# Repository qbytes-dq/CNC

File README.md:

# CNC
CNC projects

This project is for users to build a CNC projects. 

Components included are:
- PCB Etching
- etc...

TAGs will be created upon projects being available, not every commit.

SCH files are Eagle schematics.

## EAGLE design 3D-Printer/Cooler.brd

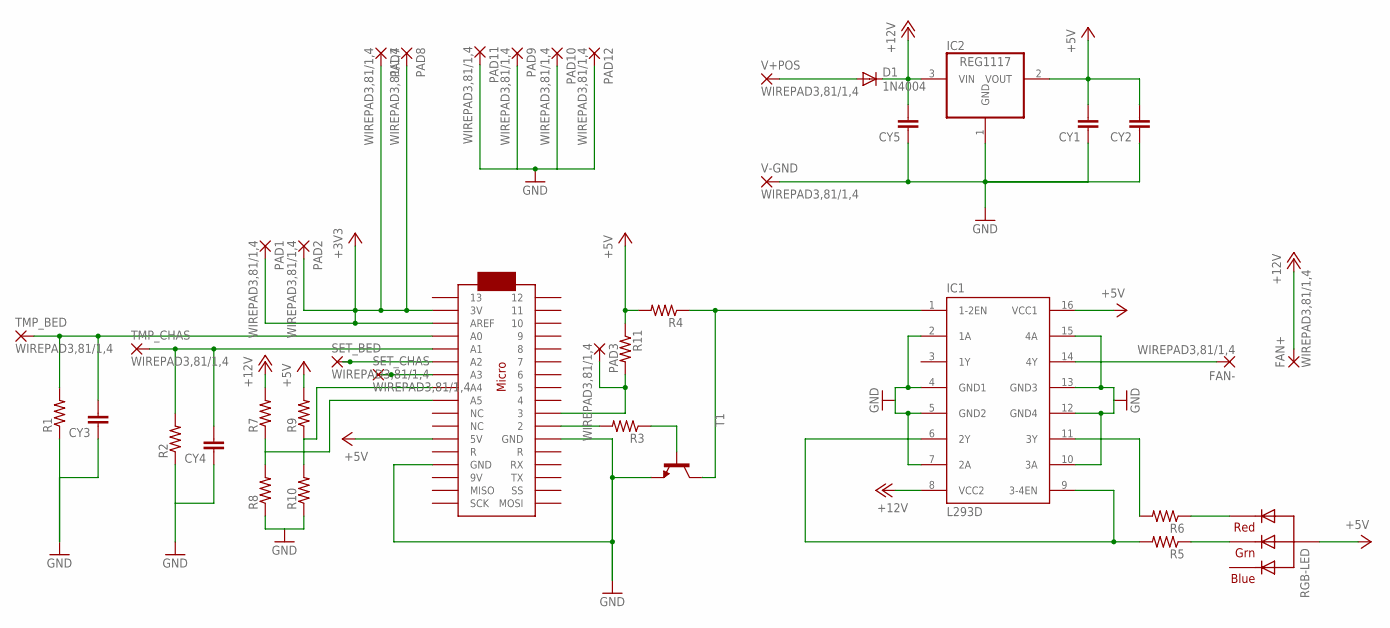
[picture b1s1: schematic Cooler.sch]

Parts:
CY1, CY2, CY3, CY4, CY5: CYYC7B5; YC7B5
D1: 1N4004; DO41-10
FAN+: WIREPAD3,81/1,4; 3,81/1,4
FAN-: WIREPAD3,81/1,4; 3,81/1,4
IC1: L293D; DIL16
IC2: REG1117; SOT223
PAD1, PAD2, PAD3, PAD7, PAD8, PAD9, PAD10, PAD11, PAD12: WIREPAD3,81/1,4; 3,81/1,4
R1, R2, R3, R4, R8, R10, R11: R-US_0309/10; 0309/10
R5, R6, R7, R9: R-US_0309/12; 0309/12
RGB-LED: RGBLED_CA-5MM; LED5MMRGB
SET_BED: WIREPAD3,81/1,4; 3,81/1,4
SET_CHAS: WIREPAD3,81/1,4; 3,81/1,4
T1: 2N2222-NPN-TO92-EBC; TO92-EBC
TMP_BED: WIREPAD3,81/1,4; 3,81/1,4
TMP_CHAS: WIREPAD3,81/1,4; 3,81/1,4
U$1: ARDUINOMICRO
V+POS: WIREPAD3,81/1,4; 3,81/1,4
V-GND: WIREPAD3,81/1,4; 3,81/1,4

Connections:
+3V3: PAD1.1, PAD2.1, PAD7.1, PAD8.1, U$1.P$32 (AREF), U$1.P$33 (3V)
+5V: CY1.2, CY2.2, IC1.16 (VCC1), IC2.2 (VOUT), R4.2, R9.2, R11.1, RGB-LED.2 (VCC), U$1.P$23 (5V)
+12V: CY5.2, D1.C, FAN+.1, IC1.8 (VCC2), IC2.3 (VIN), R7.2
GND: CY1.1, CY2.1, CY3.1, CY4.1, CY5.1, IC1.2 (1A), IC1.4 (GND1), IC1.5 (GND2), IC1.7 (2A), IC1.10 (3A), IC1.12 (GND4), IC1.13 (GND3), IC1.15 (4A), IC2.1 (GND), PAD9.1, PAD10.1, PAD11.1, PAD12.1, R1.1, R2.1, R8.1, R10.1, T1.E, U$1.P$12 (GND), U$1.P$21 (GND), V-GND.1
unnamed: R3.1, T1.B
unnamed: CY3.2, R1.2, TMP_BED.1, U$1.P$31 (A0)
unnamed: IC1.1 (1-2EN), R4.1, T1.C
unnamed: CY4.2, R2.2, TMP_CHAS.1, U$1.P$30 (A1)
unnamed: IC1.6 (2Y), IC1.9 (3-4EN), R5.2
unnamed: IC1.11 (3Y), R6.2
unnamed: R6.1, RGB-LED.1 (RED)
unnamed: R5.1, RGB-LED.3 (GREEN)
unnamed: FAN-.1, IC1.14 (4Y)
unnamed: D1.A, V+POS.1
unnamed: R3.2, U$1.P$11 (2)
unnamed: PAD3.1, R11.2, U$1.P$10 (3)
unnamed: SET_BED.1, U$1.P$29 (A2)
unnamed: SET_CHAS.1, U$1.P$28 (A3)
unnamed: R7.1, R8.2, U$1.P$26 (A5)
unnamed: R9.1, R10.2, U$1.P$27 (A4)

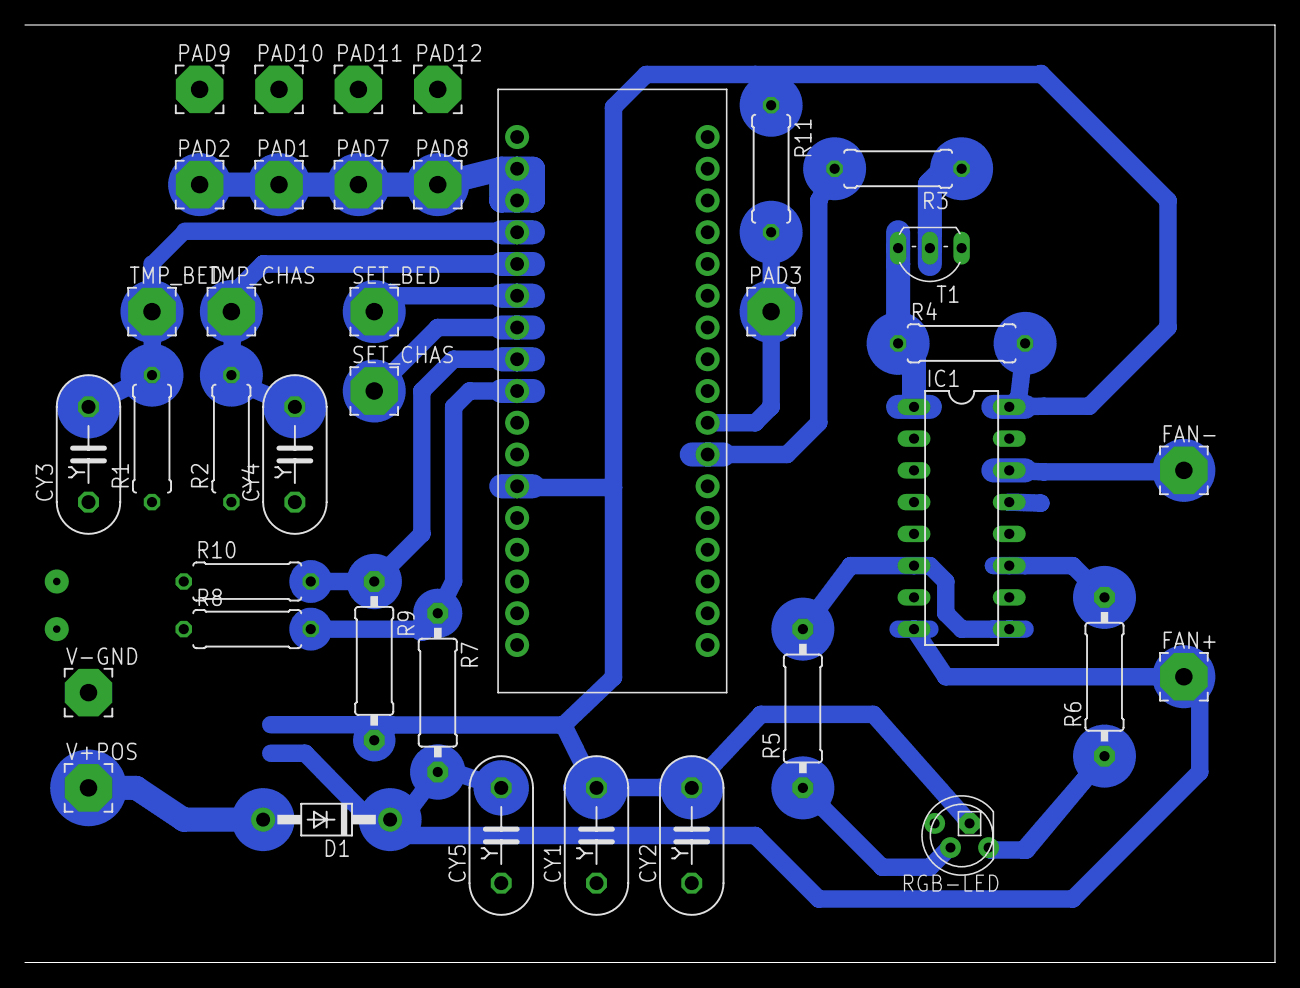
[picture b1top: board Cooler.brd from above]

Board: 2 copper layers, 100.0 x 75.0 mm, 39 parts (1 on the bottom side), 20 nets.

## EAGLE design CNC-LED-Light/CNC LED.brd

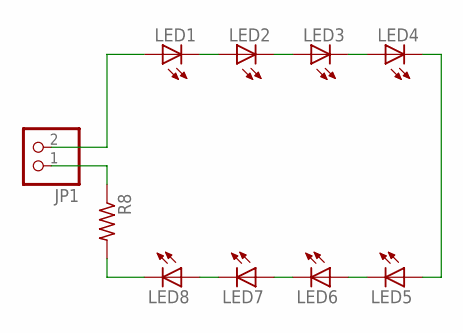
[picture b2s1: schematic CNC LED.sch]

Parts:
JP1: PINHD-1X2; 1X02
LED1, LED2, LED3, LED4, LED5, LED6, LED7, LED8: LEDCHIPLED_1206; CHIPLED_1206
R8: R-US_R1206; R1206

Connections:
unnamed: LED1.C, LED2.A
unnamed: JP1.1, R8.1
unnamed: LED2.C, LED3.A
unnamed: LED3.C, LED4.A
unnamed: LED8.C, R8.2
unnamed: LED4.C, LED5.A
unnamed: LED5.C, LED6.A
unnamed: LED6.C, LED7.A
unnamed: LED7.C, LED8.A
unnamed: JP1.2, LED1.A

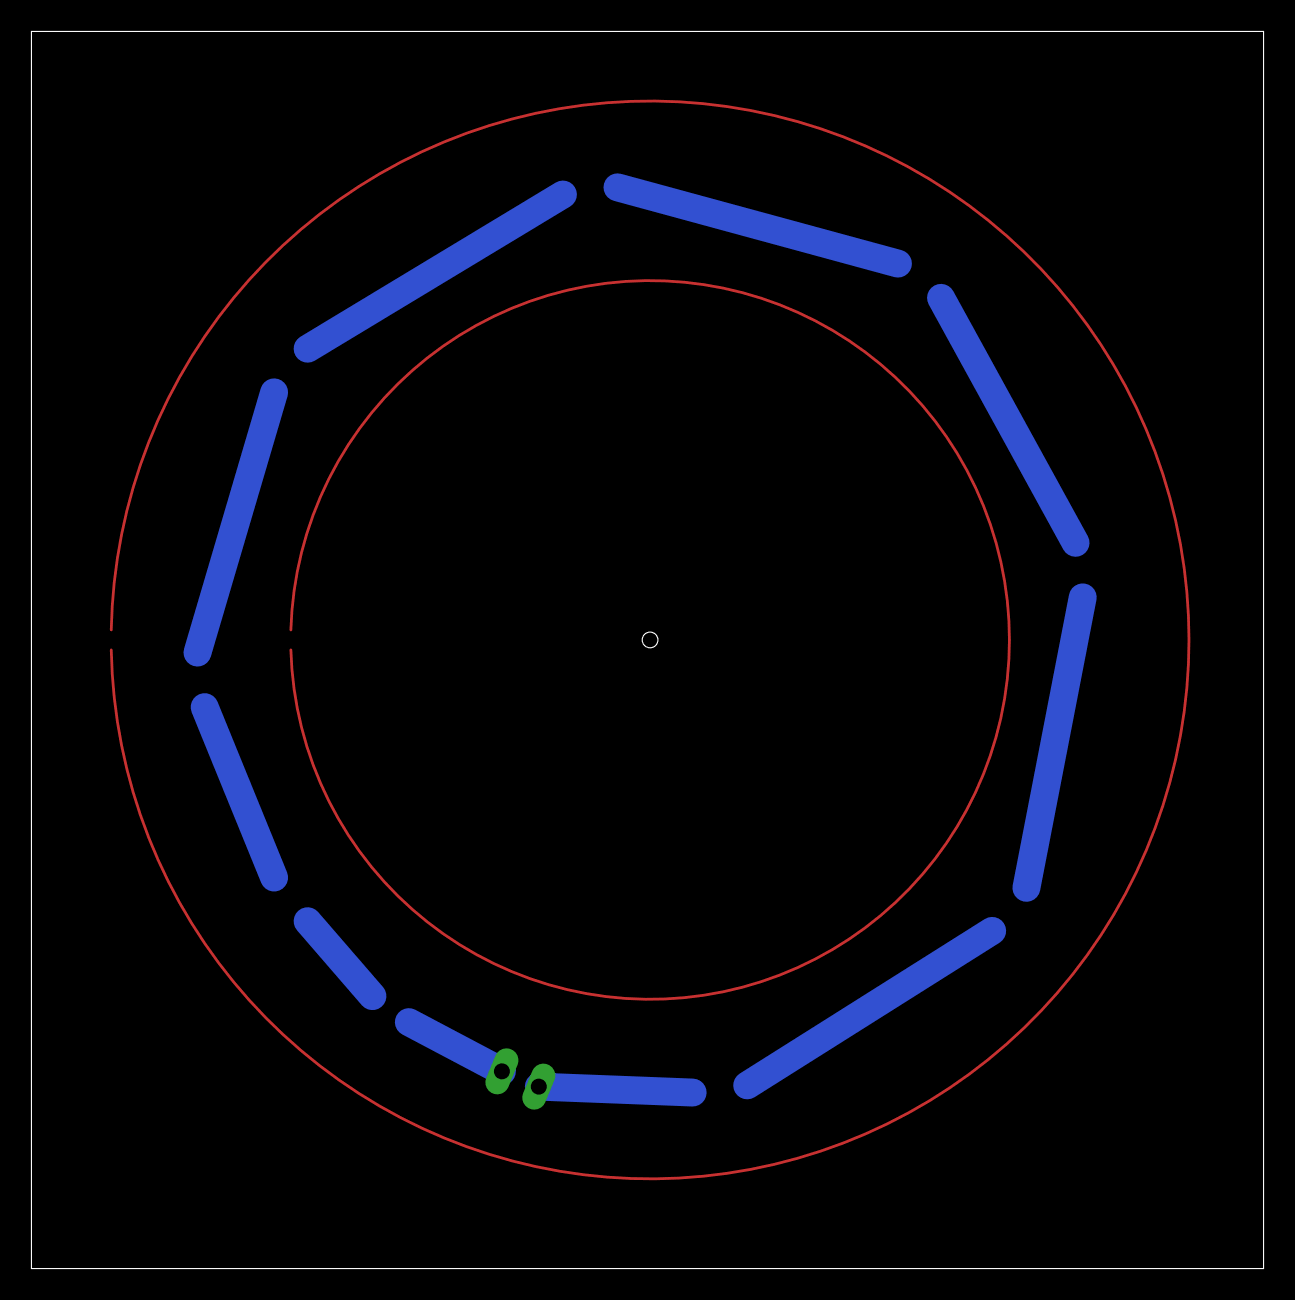
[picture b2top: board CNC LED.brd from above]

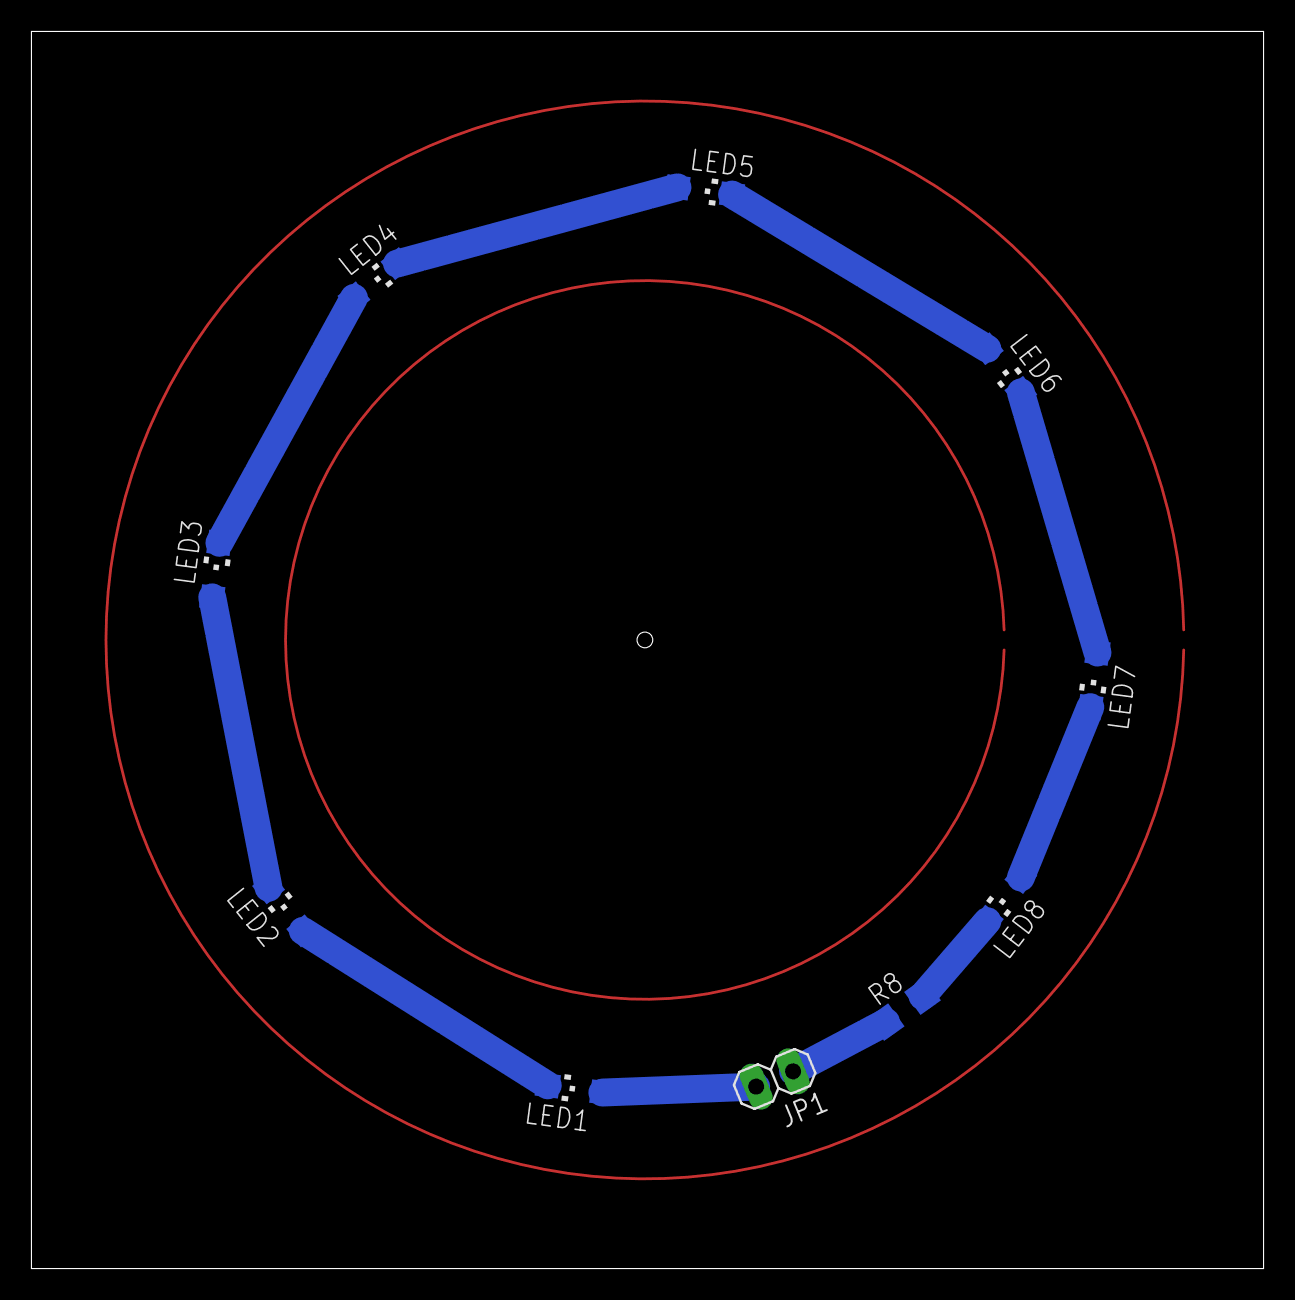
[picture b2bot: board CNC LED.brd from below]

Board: 2 copper layers, 78.4 x 78.7 mm, 10 parts (10 on the bottom side), 10 nets.

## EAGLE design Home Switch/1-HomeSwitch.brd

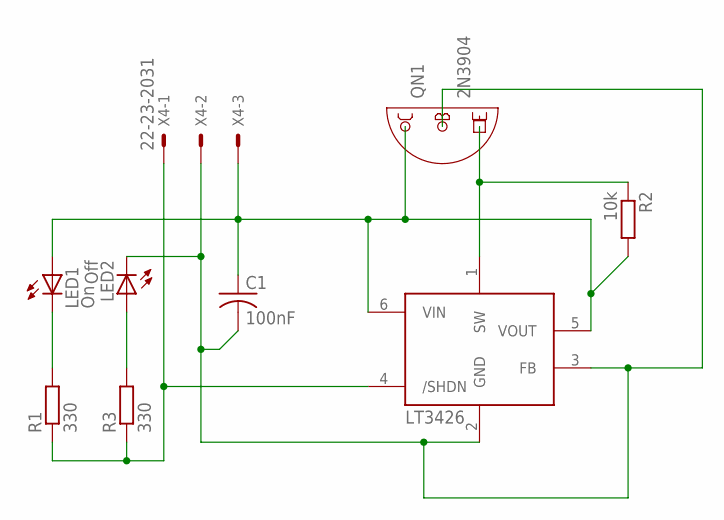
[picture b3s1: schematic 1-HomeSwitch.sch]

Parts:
C1: 100nF; C1210
IC1: 74LVG1G58GV; SOT23-6
LED1: On; LED5MM
LED2: Off; LED5MM
QN1: 2N3904; TO92
R1, R3: 330; R0805
R2: 10k; R0805
X4: 22-23-2031

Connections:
GND: C1.2, IC1.2 (GND), IC1.3 (FB), LED2.K (C), QN1.2 (B), X4.2
unnamed: LED1.K (C), R1.2
unnamed: C1.1, IC1.5 (VOUT), IC1.6 (VIN), LED1.A, QN1.1 (C), R2.2, X4.3
unnamed: IC1.1 (SW), QN1.3 (E), R2.1
unnamed: IC1.4 (/SHDN), R1.1, R3.1, X4.1
unnamed: LED2.A, R3.2

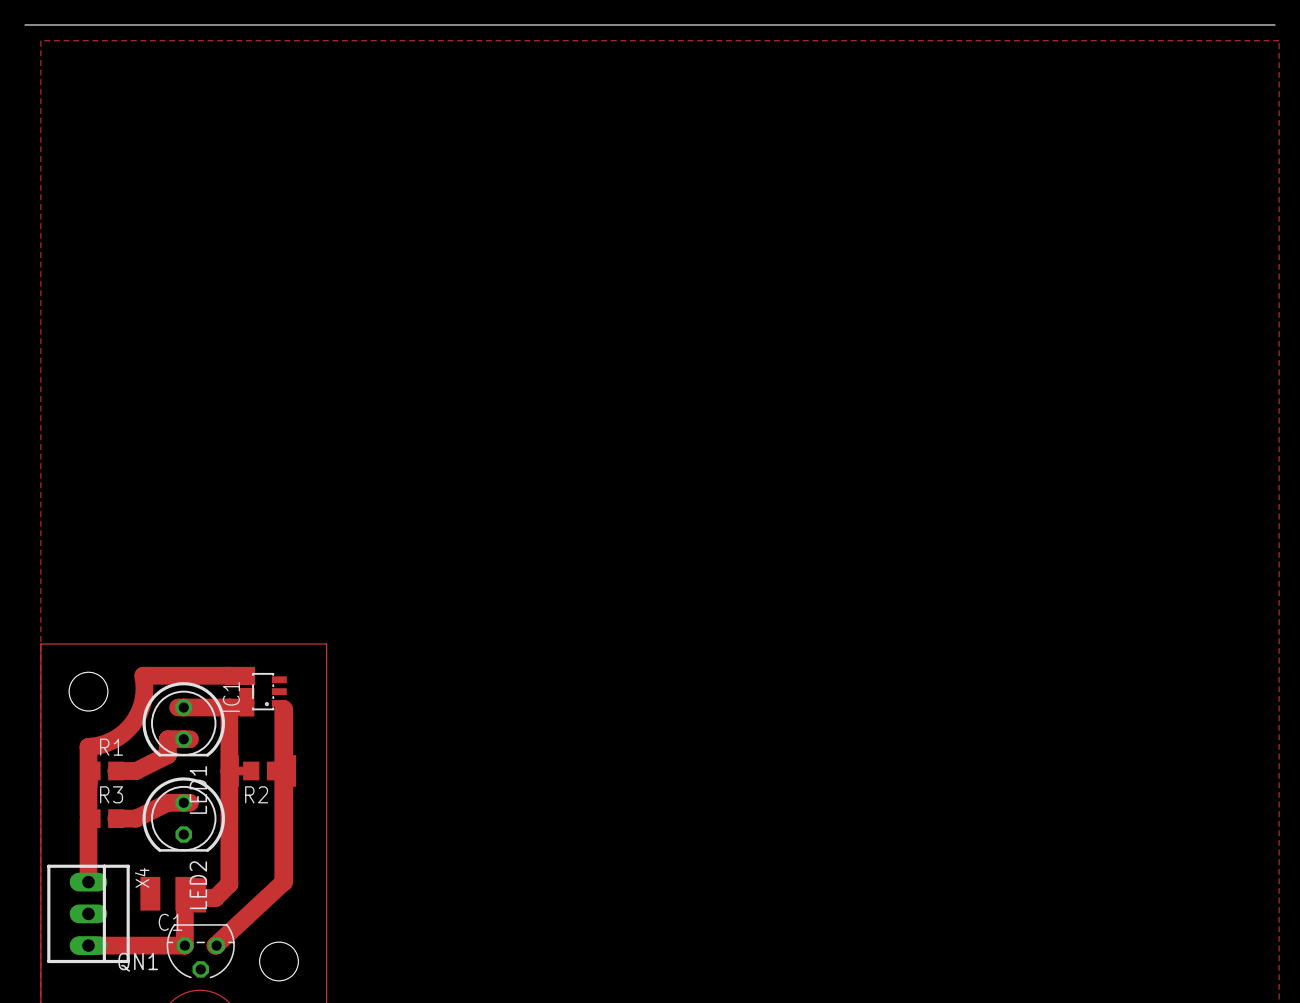
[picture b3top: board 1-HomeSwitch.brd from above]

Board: 2 copper layers, 9 parts (0 on the bottom side), 6 nets.

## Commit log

2016-11-15 Checkin
    Checking
2017-04-02 Found old sensor
    Adding to GitHub
2017-07-13 Update for Leveling
    Autoleveling updates
2017-07-13 Eagle
    Eagle sch files
2017-07-13 Revert "Update for Leveling"
    This reverts commit 38678b6c7ff8d8b3cbb829219c82c69d9fc471fe.
2017-07-15 Cooler
    Completing the COOLER for the 3D printer
2017-07-19 correct meters
    meters and serial needed reversed.
2017-07-22 Added bounce capacitor
    Corrected bounce on switch
